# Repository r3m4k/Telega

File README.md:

# Telega

## Структура проекта

Проект состоит из нескольких самостоятельных частей:

- `Embedded` - прошивка для STM32F3Discovery, протокол обмена, драйверы датчиков и прикладная логика МК.
- `Python` - GUI-приложение для ПК, слой связи с МК, сохранение данных и вспомогательные модули анализа.
- `KiCad` - файлы печатной платы. В рамках этого README описывается только наличие раздела, без разбора содержимого.
- `Kompas3d` - механические модели и сборки. Файлы CAD не анализируются подробно.
- `Список комплектующих.csv` - перечень компонентов проекта.

## GUI-приложение для ПК

GUI находится в каталоге `Python` и запускается из `Python/main.py`. Приложение написано на PyQt5 и предназначено для работы с путеизмерительной тележкой через COM-порт: настройка подключения, запуск служебных стадий МК, отображение текущих показаний и сохранение результатов измерений.

### Запуск

Рекомендуемый запуск из корня репозитория:

```bash
python -m venv Python/.venv
Python/.venv/Scripts/pip install -r Python/requirements.txt
Python/.venv/Scripts/python Python/main.py
```

На Linux путь к интерпретатору виртуального окружения будет `Python/.venv/bin/python`.

### Возможности приложения

- выбор директории сохранения и шаблона имени файлов;
- выбор и обновление списка COM-портов;
- запуск рукопожатия с МК после применения настроек;
- запуск набора статического буфера перед проездом;
- запуск и завершение измерительного проезда;
- отображение текущих значений `Acc_X`, `Acc_Y`, `Acc_Z`, `Gyro_X`, `Gyro_Y`, `Gyro_Z` и кода ДПП;
- сохранение данных статического буфера и проезда в CSV;
- вывод пользовательских сообщений, предупреждений и ошибок в журнале окна.

Типовой рабочий сценарий описан подробнее в `Python/docs/USER_GUIDE.md`.

### Основные модули

- `Python/main.py` - точка входа, создание `QApplication` и главного окна.
- `Python/gui/main_window.py` - главное окно, координирующее интерфейс, сессию связи и переключение пользовательских стадий.
- `Python/gui/program_stages` - реализации стадий настройки, статического буфера и измерений, а также контракт главного окна, необходимый этим стадиям.
- `Python/gui/ui/main_window.ui` - Qt Designer-разметка интерфейса; рядом лежат графические ресурсы `telega.png` и `update.png`.
- `Python/gui/com_port_settings.py` и `Python/gui/saving_params.py` - работа с настройками COM-порта и параметрами сохранения.
- `Python/gui/com_port_reader.py` - мост между GUI и низкоуровневой сессией МК. Запускает отдельный процесс для обмена с устройством и прокидывает данные/события в GUI через Qt-сигналы.
- `Python/telega_session/data_storage.py` - потоковая запись пакетов `TelegaData` в CSV в дочерней сессии МК.
- `Python/gui/data_visualization.py` - обновление LCD-индикаторов текущими значениями телеметрии.
- `Python/telega_session` - проектный слой общения с тележкой: COM-порт, декодер протокола, контроллер команд и функция запуска сессии.
- `Python/async_mc_controller` - более общий асинхронный слой для источников байтов, декодирования, контроллера, шины сигналов, логирования и конфигурации.
- `Python/app_config` и `Python/logger` - конфигурация приложения на Pydantic и настройка логирования.
- `Python/data_analys` и `Python/plotting` - вспомогательные модули для постобработки, фильтрации, расчета траектории и построения графиков.

### Поток данных

После применения настроек главное окно создаёт конфигурацию COM-порта и запускает `ComPortReader`. Низкоуровневая сессия работает в отдельном процессе через `multiprocessing`, читает байтовый поток с устройства, декодирует пакеты протокола и потоково сохраняет их в CSV. В GUI передаётся только последний пакет не чаще одного раза в 500 мс для обновления индикаторов; служебные события и ошибки передаются отдельной очередью. Главное окно задаёт путь CSV-файла и переключает доступные действия пользователя согласно текущей стадии работы.

### Сохраняемые данные

Во время набора статического буфера создается файл вида:

```text
{шаблонное_название}_static_init_{номер_проезда}.csv
```

Во время измерительного проезда создается файл вида:

```text
{шаблонное_название}_measuring_{номер_проезда}.csv
```

CSV пишется в UTF-8 с полями:

```text
PackageNum DppCode AccX AccY AccZ GyroX GyroY GyroZ Temp
```

Настройки приложения сохраняются в `Python/app_config/settings.json`; файл относится к локальным runtime-данным и не обязан храниться в репозитории.

## Прошивка для STM32F3Discovery

Пользовательская часть прошивки расположена в `Embedded/user` и написана как C++-слой поверх STM32F30x Standard Peripheral Library, USB VCP и библиотек датчиков платы STM32F3Discovery. Проект устроен почти как header-only фреймворк: прикладной сценарий находится в `src/main.cpp`, а драйверы, контейнеры, фильтры, протоколы и обвязка периферии вынесены в заголовочные модули `inc`.

### Общая структура

- `src/main.cpp` - точка входа, инициализация оборудования, главный цикл, стадии программы, обработчики команд и системные функции.
- `inc/main.h` - C/C++ мост к STM32 SPL, USB VCP, CMSIS и функциям пользовательского слоя.
- `inc/Common` - общие типы, константы, `TriaxialData` и базовый механизм регистрации обработчиков прерываний.
- `inc/Periph` - GPIO, EXTI и светодиоды платы.
- `inc/Timers` - обертки над аппаратными таймерами STM32, конфигурации и descriptor-классы.
- `inc/Sensors` - драйверы L3GD20, LSM303DLHC и масштабирование датчиков.
- `inc/Filters` - статистика, N-sigma фильтр и фильтр Калмана.
- `inc/DataContainers` - очереди фиксированного размера, включая SPSC-очередь для обмена между IRQ и main.
- `inc/Communication` - сообщения, пакеты, декодеры, USB VCP и USART.
- `inc/aaa_Project_Files` - доменная логика проекта: команды, пакет телеметрии, декодер входящих команд и датчик пройденного пути.

### Инициализация и прерывания

При старте `main()` копирует таблицу векторов прерываний из flash в пользовательскую таблицу `_user_vector_table` в RAM, переключает `SCB->VTOR` на эту таблицу и затем инициализирует оборудование через `InitAll()`. Такой подход позволяет C++-объектам регистрировать собственные обработчики IRQ во время инициализации.

Механизм регистрации прерываний реализован через CRTP-класс `BaseIRQDevice`. Конкретные устройства, например таймеры или EXTI-пины, наследуются от него, сохраняют указатель на активный экземпляр и записывают статический обработчик в пользовательскую таблицу векторов. При срабатывании IRQ статический обработчик перенаправляет вызов в метод `irq_handler()` нужного объекта.

### Основной цикл и стадии программы

Главный цикл прошивки работает как простой диспетчер событий. Сначала он выполняет накопленные отложенные команды из `command_manager.command_queue`, затем при необходимости переключает текущую стадию из `program_stage_queue`, после чего вызывает `init()` новой стадии один раз и `execute()` на каждом проходе цикла.

Поддерживаемые стадии:

- `FooStage` - состояние ожидания: таймеры остановлены, датчики периодически читаются для поддержания их рабочего состояния.
- `StaticStage` - статический сбор начальных данных: формируется `InitFrameNum` телеметрических пакетов, после чего отправляется `END_OF_STATIC_INIT`.
- `MeasuringStage` - рабочее измерение: по тику `TIM3` читаются датчики, данные фильтруются, упаковываются и отправляются на ПК.

### Таймеры

В прошивке используются два таймера общего назначения:

- `TIM3` - основной таймер измерений. Его IRQ переключает светодиод `LED9`, выставляет флаг нового периода измерений и увеличивает счетчик времени `tick_counter`.
- `TIM4` - таймер индикации состояния. Его IRQ переключает `LED6` и `LED7`.

Таймеры описаны шаблонными классами `Timer2`, `Timer3`, `Timer4`, которые принимают пользовательский обработчик прерывания как compile-time параметр. Это позволяет вызывать обработчик без виртуальных функций и без runtime-диспетчеризации.

### Датчики и фильтрация

Прошивка работает с датчиками платы STM32F3Discovery:

- `L3GD20` - гироскоп, данные угловой скорости.
- `LSM303DLHC` - акселерометр и температурный датчик; магнитометр в текущей конфигурации отключен.
- `DppSensor` - датчик пройденного пути: импульсы приходят на EXTI-вход `PC1`, направление считывается с `PC3`.

Перед отправкой телеметрии данные акселерометра, гироскопа и температуры проходят через `NSigmaFilter`. Для ускорения и угловой скорости используется фильтр `NSigmaFilter<TriaxialData, 4, 16>`, для температуры - `NSigmaFilter<float, 1, 16>`. Фильтр отбрасывает выбросы по правилу N-sigma и накапливает итоговое среднее.

### Связь с ПК и протокол

Основной канал связи с ПК - USB Virtual COM Port. Входящие данные принимаются в `UserEP3_OUT_Callback()`, преобразуются в `Messages::SizedMessage<VCP_BUFFER_SIZE>` и передаются в `UsbPort`, где поток байтов разбирается `DecoderTelega`.

Входящий командный протокол:

- header: `0xE7 0x7E`;
- format: `0xAB`;
- length: длина поля данных;
- data: код команды;
- checksum: младший байт суммы предыдущих байтов пакета.

`DecoderTelega` отвечает только за входящий поток команд. Он находит команду в списках `urgent_commands` и `deferred_commands` менеджера команд. Срочные команды выполняются сразу в контексте обработчика приема, отложенные команды помещаются в SPSC-очередь и выполняются позже в основном цикле.

Поддерживаемые команды:

- `0xff 0xff` - перезагрузка МК.
- `0xaa 0x00` - переход в `FooStage`.
- `0xaa 0x02` - переход в `MeasuringStage`.
- `0xaa 0x03` - переход в `StaticStage`.
- `HANDSHAKE_ACK`, `HEARTBEAT_ACK` - текстовые служебные команды, на которые МК отвечает собственными ACK-сообщениями.

### Исходящие пакеты

Телеметрия отправляется через `TelegaPackage`. Пакет содержит:

- счетчик времени `tick_counter`;
- ускорение `acc_value`;
- угловую скорость `gyro_value`;
- температуру `temp_value`;
- код датчика пройденного пути `dpp_code`;
- контрольную сумму.

Текстовые служебные ответы формируются через `MessagePackage`: подтверждение команды, handshake ACK, heartbeat ACK, сообщение об ошибке и окончание статической инициализации.

### Соглашения проекта

Прошивка рассчитана на доверенный ПК-клиент, который отправляет небольшие корректные команды и не перегружает очередь команд. Переполнение очередей и чрезмерная длина входящих пакетов считаются нарушением протокольного соглашения, а не штатным режимом работы. Частота таймера измерений должна быть согласована со временем чтения датчиков, фильтрации и отправки пакета так, чтобы обработка успевала завершиться до следующего периода измерений.

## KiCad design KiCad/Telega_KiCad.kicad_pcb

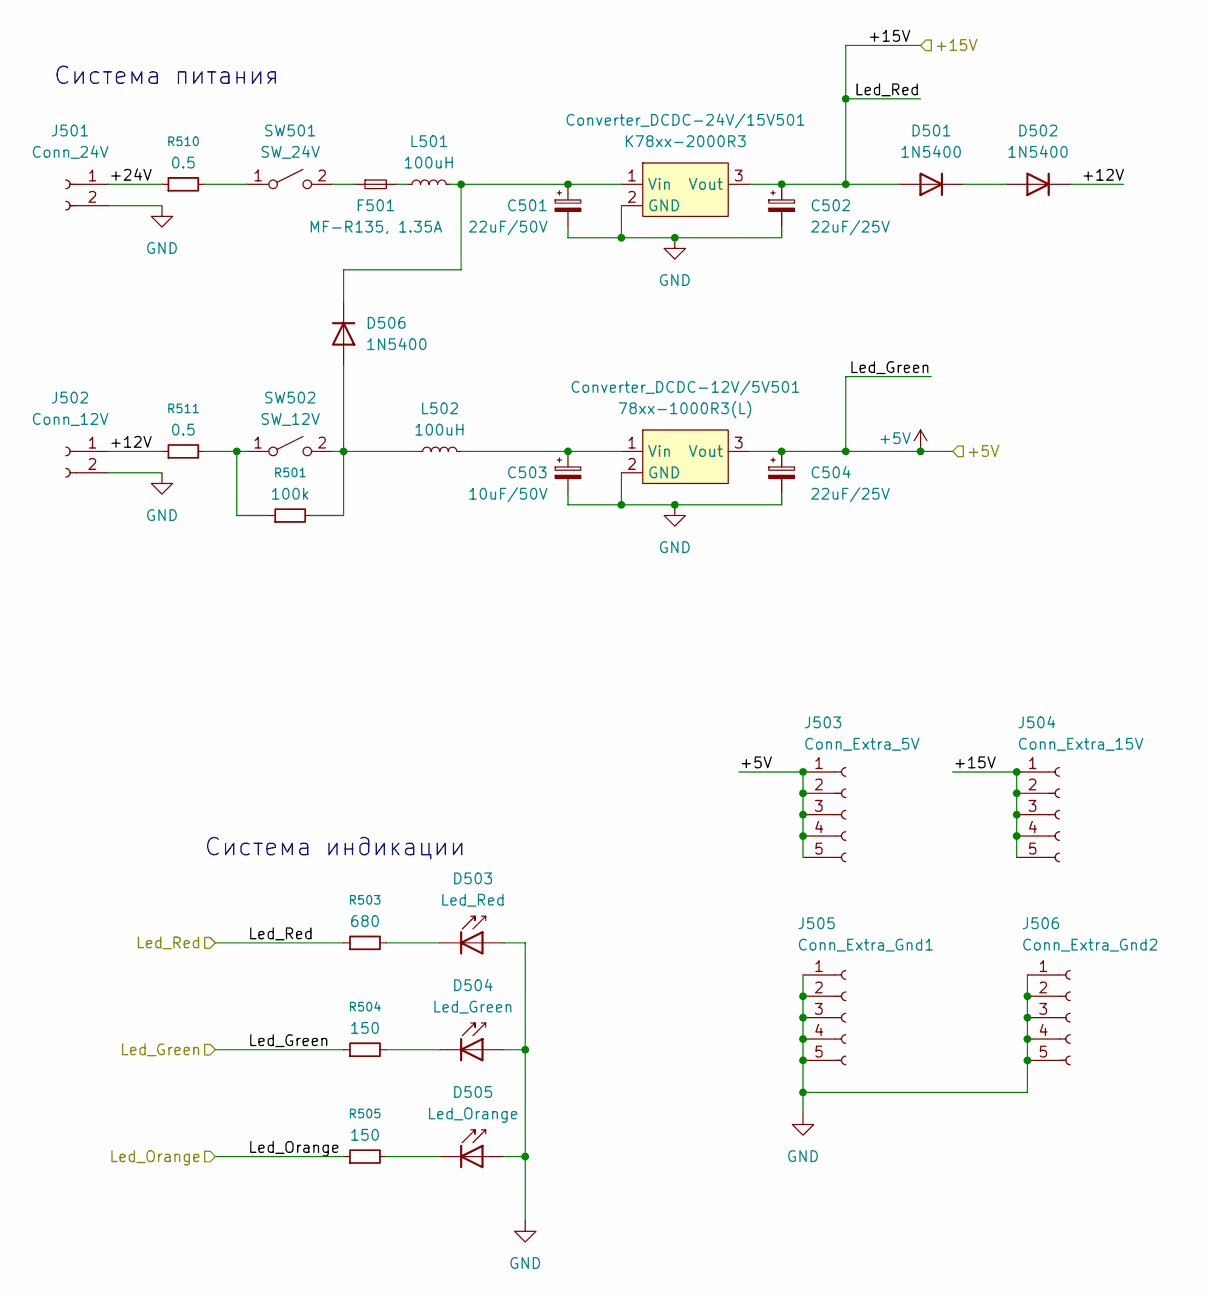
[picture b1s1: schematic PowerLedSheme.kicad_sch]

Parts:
C501: 22uF/50V; CP_Radial_D8.0mm_P5.00mm
C502, C504: 22uF/25V; CP_Radial_D8.0mm_P5.00mm
C503: 10uF/50V; CP_Radial_D8.0mm_P5.00mm
Converter_DCDC-12V/5V501: 78xx-1000R3(L); Converter_DCDC_RECOM_R-78B-2.0_THT
Converter_DCDC-24V/15V501: K78xx-2000R3; Converter_DCDC_RECOM_R-78B-2.0_THT
D501, D502, D506: 1N5400; D_DO-201AD_P15.24mm_Horizontal
D503: Led_Red; SolderWire-1sqmm_1x02_P5.4mm_D1.4mm_OD2.7mm
D504: Led_Green; SolderWire-1sqmm_1x02_P5.4mm_D1.4mm_OD2.7mm
D505: Led_Orange; SolderWire-1sqmm_1x02_P5.4mm_D1.4mm_OD2.7mm
F501: MF-R135, 1.35А; Fuse_Bourns_MF-RG300
J501: Conn_24V; Molex_KK-254_AE-6410-02A_1x02_P2.54mm_Vertical
J502: Conn_12V; Molex_KK-254_AE-6410-02A_1x02_P2.54mm_Vertical
J503: Conn_Extra_5V; SolderWire-1sqmm_1x05_P5.4mm_D1.4mm_OD2.7mm
J504: Conn_Extra_15V; SolderWire-1sqmm_1x05_P5.4mm_D1.4mm_OD2.7mm
J505: Conn_Extra_Gnd1; SolderWire-1sqmm_1x05_P5.4mm_D1.4mm_OD2.7mm
J506: Conn_Extra_Gnd2; SolderWire-1sqmm_1x05_P5.4mm_D1.4mm_OD2.7mm
L501, L502: 100uH; L_Radial_D9.5mm_P5.00mm_Fastron_07HVP
R501: 100k; R_Axial_DIN0516_L15.5mm_D5.0mm_P25.40mm_Horizontal
R503: 680; R_Axial_DIN0516_L15.5mm_D5.0mm_P25.40mm_Horizontal
R504, R505: 150; R_Axial_DIN0516_L15.5mm_D5.0mm_P25.40mm_Horizontal
R510, R511: 0.5; R_Axial_Power_L38.0mm_W6.4mm_P40.64mm
SW501: SW_24V; SolderWire-1.5sqmm_1x02_P7.8mm_D1.7mm_OD3.9mm
SW502: SW_12V; SolderWire-1.5sqmm_1x02_P7.8mm_D1.7mm_OD3.9mm

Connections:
+5V: C504.1, Converter_DCDC-12V/5V501.3 (Vout), J503.1, J503.2, J503.3, J503.4, J503.5, R504.1; also elsewhere on the board
/+15V: C502.1, Converter_DCDC-24V/15V501.3 (Vout), D501.2 (A), J504.1, J504.2, J504.3, J504.4, J504.5, R503.1; also elsewhere on the board
/Led_Orange: R505.1; also elsewhere on the board
/PowerLedSheme/+12V: D502.1 (K), J502.1, R511.1
/PowerLedSheme/+24V: J501.1, R510.1
GND: C501.2, C502.2, C503.2, C504.2, Converter_DCDC-12V/5V501.2 (GND), Converter_DCDC-24V/15V501.2 (GND), D503.2 (A), D504.2 (A), D505.2 (A), J501.2, J502.2, J505.1, J505.2, J505.3, J505.4, J505.5, J506.1, J506.2, J506.3, J506.4, J506.5; also elsewhere on the board
unnamed: C503.1, Converter_DCDC-12V/5V501.1 (Vin), L502.2
unnamed: C501.1, Converter_DCDC-24V/15V501.1 (Vin), D506.1 (K), L501.2
unnamed: D501.1 (K), D502.2 (A)
unnamed: D503.1 (K), R503.2
unnamed: D504.1 (K), R504.2
unnamed: D505.1 (K), R505.2
unnamed: D506.2 (A), L502.1, R501.2, SW502.2 (B)
unnamed: F501.2, L501.1
unnamed: R510.2, SW501.1 (A)
unnamed: F501.1, SW501.2 (B)
unnamed: R501.1, R511.2, SW502.1 (A)

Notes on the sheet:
Система питания
Система индикации

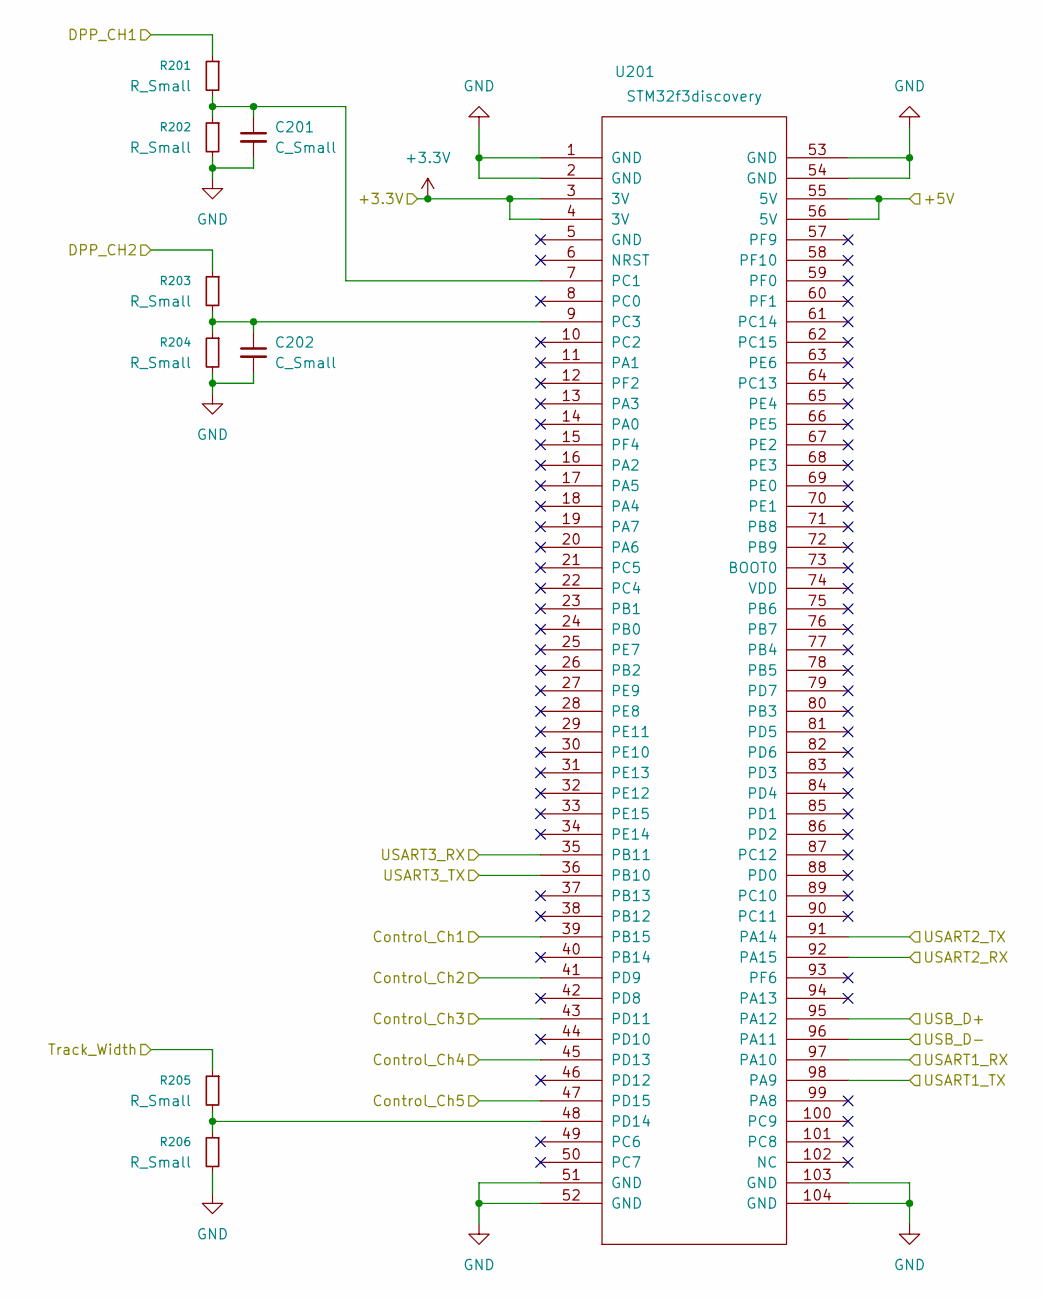
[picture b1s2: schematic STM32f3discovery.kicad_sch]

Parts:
C201, C202: C_Small; CP_Radial_D8.0mm_P5.00mm
R201, R202, R203, R204, R205, R206: R_Small; R_Axial_DIN0207_L6.3mm_D2.5mm_P15.24mm_Horizontal
U201: STM32f3discovery

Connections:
+3.3V: U201.3 (3V), U201.4 (3V)
+5V: U201.55 (5V), U201.56 (5V); also elsewhere on the board
/Control_Ch1: U201.39 (PB15); also elsewhere on the board
/Control_Ch2: U201.41 (PD9); also elsewhere on the board
/Control_Ch3: U201.43 (PD11); also elsewhere on the board
/Control_Ch4: U201.45 (PD13); also elsewhere on the board
/Control_Ch5: U201.47 (PD15); also elsewhere on the board
/DPP_CH1: R201.1; also elsewhere on the board
/DPP_CH2: R203.1; also elsewhere on the board
/Track_Width: R205.1; also elsewhere on the board
/USART1_RX: U201.97 (PA10); also elsewhere on the board
/USART1_TX: U201.98 (PA9); also elsewhere on the board
/USART2_RX: U201.92 (PA15); also elsewhere on the board
/USART2_TX: U201.91 (PA14); also elsewhere on the board
/USART3_RX: U201.35 (PB11); also elsewhere on the board
/USART3_TX: U201.36 (PB10); also elsewhere on the board
/USB_D+: U201.95 (PA12); also elsewhere on the board
/USB_D-: U201.96 (PA11); also elsewhere on the board
GND: C201.2, C202.2, R202.2, R204.2, R206.2, U201.1 (GND), U201.2 (GND), U201.51 (GND), U201.52 (GND), U201.53 (GND), U201.54 (GND), U201.103 (GND), U201.104 (GND); also elsewhere on the board
unnamed: C201.1, R201.2, R202.1, U201.7 (PC1)
unnamed: C202.1, R203.2, R204.1, U201.9 (PC3)
unnamed: R205.2, R206.1, U201.48 (PD14)

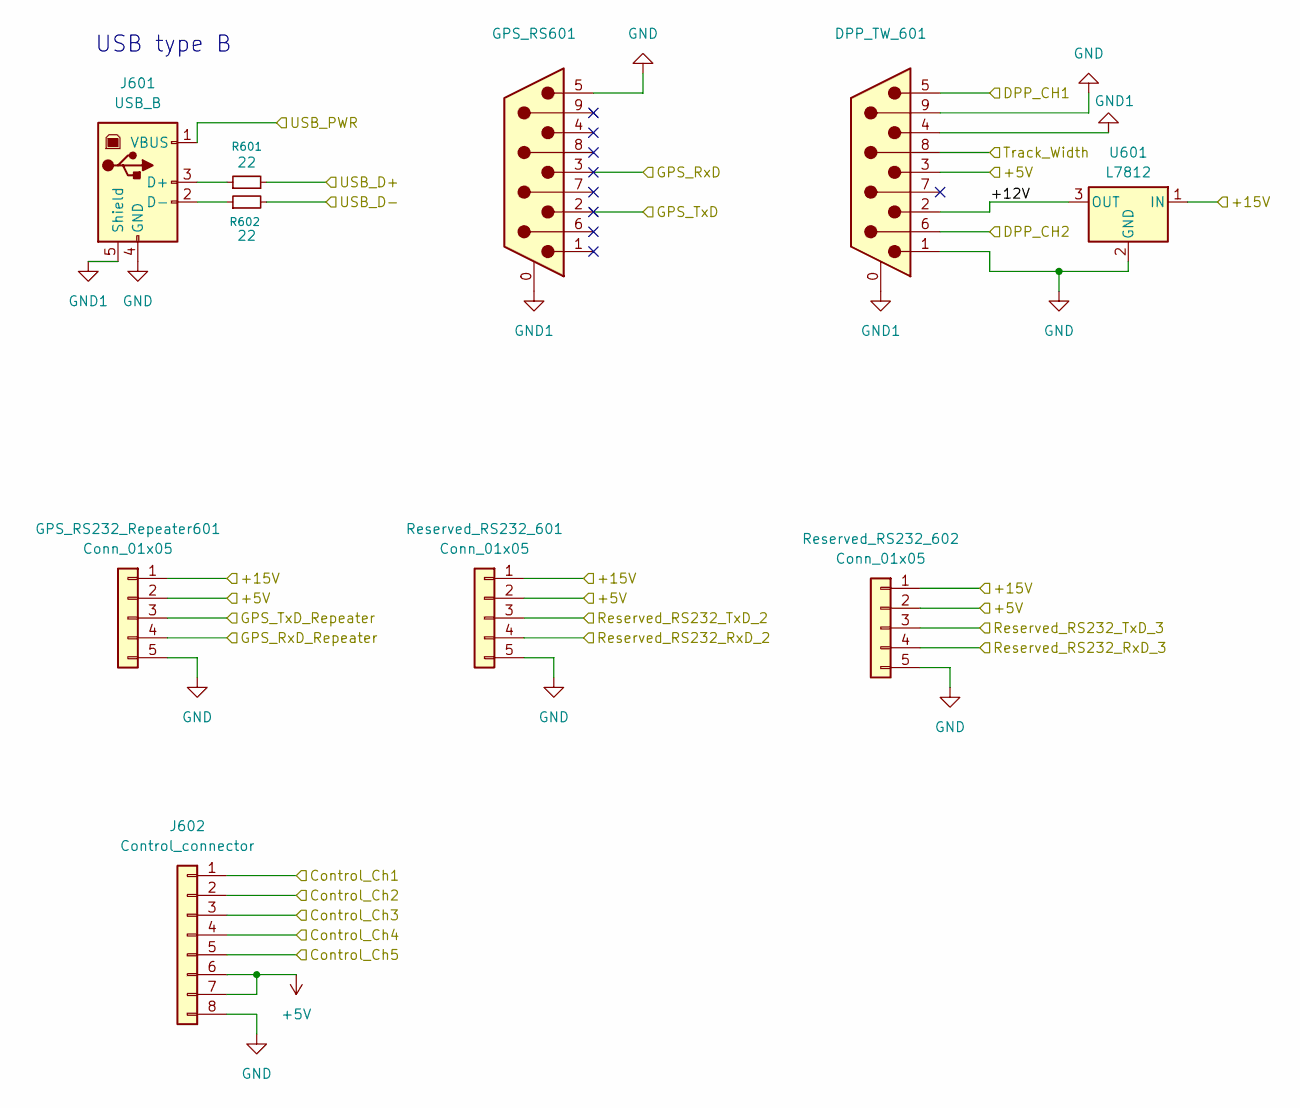
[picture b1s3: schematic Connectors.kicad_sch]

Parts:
DPP_TW_601: DE9_Pins_MountingHoles; DSUB-9_Pins_Horizontal_P2.77x2.84mm_EdgePinOffset7.70mm_Hou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
GPS_RS232_Repeater601: Conn_01x05; SolderWire-1sqmm_1x05_P5.4mm_D1.4mm_OD2.7mm
GPS_RS601: DE9_Pins_MountingHoles; DSUB-9_Pins_Horizontal_P2.77x2.84mm_EdgePinOffset7.70mm_Hou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
J601: USB_B; USB_B_Lumberg_2411_02_Horizontal
J602: Control_connector; Molex_KK-254_AE-6410-08A_1x08_P2.54mm_Vertical
R601, R602: 22; R_1206_3216Metric
Reserved_RS232_601, Reserved_RS232_602: Conn_01x05; SolderWire-1sqmm_1x05_P5.4mm_D1.4mm_OD2.7mm
U601: L7812; TO-220-3_Vertical

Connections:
+5V: DPP_TW_601.3, GPS_RS232_Repeater601.2, J602.6, J602.7, Reserved_RS232_601.2, Reserved_RS232_602.2; also elsewhere on the board
/+15V: GPS_RS232_Repeater601.1, Reserved_RS232_601.1, Reserved_RS232_602.1, U601.1 (IN); also elsewhere on the board
/Connectors/+12V: DPP_TW_601.2, U601.3 (OUT)
/Control_Ch1: J602.1; also elsewhere on the board
/Control_Ch2: J602.2; also elsewhere on the board
/Control_Ch3: J602.3; also elsewhere on the board
/Control_Ch4: J602.4; also elsewhere on the board
/Control_Ch5: J602.5; also elsewhere on the board
/DPP_CH1: DPP_TW_601.5; also elsewhere on the board
/DPP_CH2: DPP_TW_601.6; also elsewhere on the board
/GPS_RxD: GPS_RS601.3; also elsewhere on the board
/GPS_RxD_Repeater: GPS_RS232_Repeater601.4; also elsewhere on the board
/GPS_TxD: GPS_RS601.2; also elsewhere on the board
/GPS_TxD_Repeater: GPS_RS232_Repeater601.3; also elsewhere on the board
/Led_Orange: J601.1 (VBUS); also elsewhere on the board
/Reserved_RS232_RxD_2: Reserved_RS232_601.4; also elsewhere on the board
/Reserved_RS232_RxD_3: Reserved_RS232_602.4; also elsewhere on the board
/Reserved_RS232_TxD_2: Reserved_RS232_601.3; also elsewhere on the board
/Reserved_RS232_TxD_3: Reserved_RS232_602.3; also elsewhere on the board
/Track_Width: DPP_TW_601.8; also elsewhere on the board
/USB_D+: R601.2; also elsewhere on the board
/USB_D-: R602.2; also elsewhere on the board
GND: DPP_TW_601.1, DPP_TW_601.9, GPS_RS232_Repeater601.5, GPS_RS601.5, J601.4 (GND), J602.8, Reserved_RS232_601.5, Reserved_RS232_602.5, U601.2 (GND); also elsewhere on the board
GND1: DPP_TW_601.0 (PAD), DPP_TW_601.4, GPS_RS601.0 (PAD), J601.5 (Shield)
unnamed: J601.3 (D+), R601.1
unnamed: J601.2 (D-), R602.1

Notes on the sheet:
USB type B

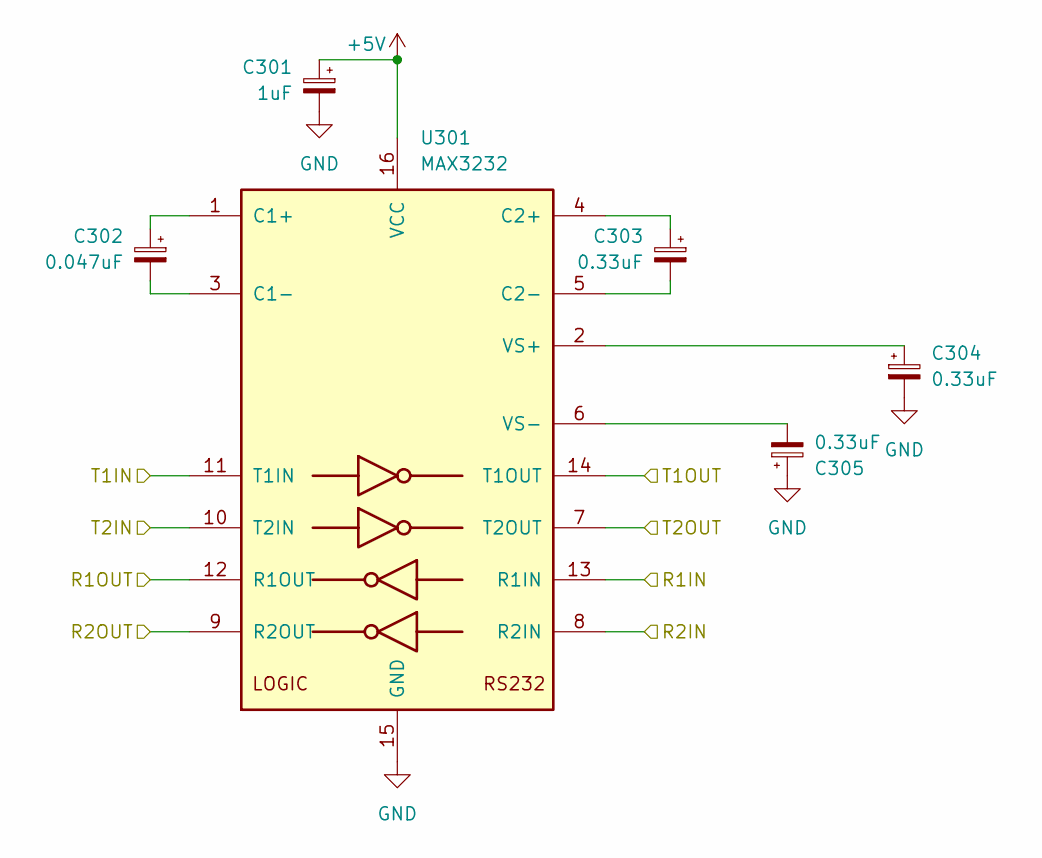
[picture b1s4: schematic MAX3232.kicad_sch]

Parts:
C301: 1uF; CP_EIA-2012-12_Kemet-R_HandSolder
C302: 0.047uF; CP_EIA-2012-12_Kemet-R_HandSolder
C303, C304, C305: 0.33uF; CP_EIA-2012-12_Kemet-R_HandSolder
U301: MAX3232; SOIC-16W_7.5x10.3mm_P1.27mm

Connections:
+5V: C301.1, U301.16 (VCC); also elsewhere on the board
/GPS_RxD: U301.14 (T1OUT); also elsewhere on the board
/GPS_RxD_Repeater: U301.7 (T2OUT); also elsewhere on the board
/GPS_TxD: U301.13 (R1IN); also elsewhere on the board
/GPS_TxD_Repeater: U301.8 (R2IN); also elsewhere on the board
/USART1_RX: U301.9 (R2OUT), U301.12 (R1OUT); also elsewhere on the board
/USART1_TX: U301.10 (T2IN), U301.11 (T1IN); also elsewhere on the board
GND: C301.2, C304.2, C305.1, U301.15 (GND); also elsewhere on the board
unnamed: C302.1, U301.1 (C1+)
unnamed: C302.2, U301.3 (C1-)
unnamed: C303.1, U301.4 (C2+)
unnamed: C303.2, U301.5 (C2-)
unnamed: C304.1, U301.2 (VS+)
unnamed: C305.2, U301.6 (VS-)

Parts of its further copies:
C401: 1uF; CP_EIA-2012-12_Kemet-R_HandSolder
C402: 0.047uF; CP_EIA-2012-12_Kemet-R_HandSolder
C403, C404, C405: 0.33uF; CP_EIA-2012-12_Kemet-R_HandSolder
U401: MAX3232; SOIC-16W_7.5x10.3mm_P1.27mm

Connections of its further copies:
+5V: C401.1, U401.16 (VCC); also elsewhere on the board
/Reserved_RS232_RxD_2: U401.14 (T1OUT); also elsewhere on the board
/Reserved_RS232_RxD_3: U401.7 (T2OUT); also elsewhere on the board
/Reserved_RS232_TxD_2: U401.13 (R1IN); also elsewhere on the board
/Reserved_RS232_TxD_3: U401.8 (R2IN); also elsewhere on the board
/USART2_RX: U401.12 (R1OUT); also elsewhere on the board
/USART2_TX: U401.11 (T1IN); also elsewhere on the board
/USART3_RX: U401.9 (R2OUT); also elsewhere on the board
/USART3_TX: U401.10 (T2IN); also elsewhere on the board
GND: C401.2, C404.2, C405.1, U401.15 (GND); also elsewhere on the board
unnamed: C402.1, U401.1 (C1+)
unnamed: C402.2, U401.3 (C1-)
unnamed: C403.1, U401.4 (C2+)
unnamed: C403.2, U401.5 (C2-)
unnamed: C404.1, U401.2 (VS+)
unnamed: C405.2, U401.6 (VS-)

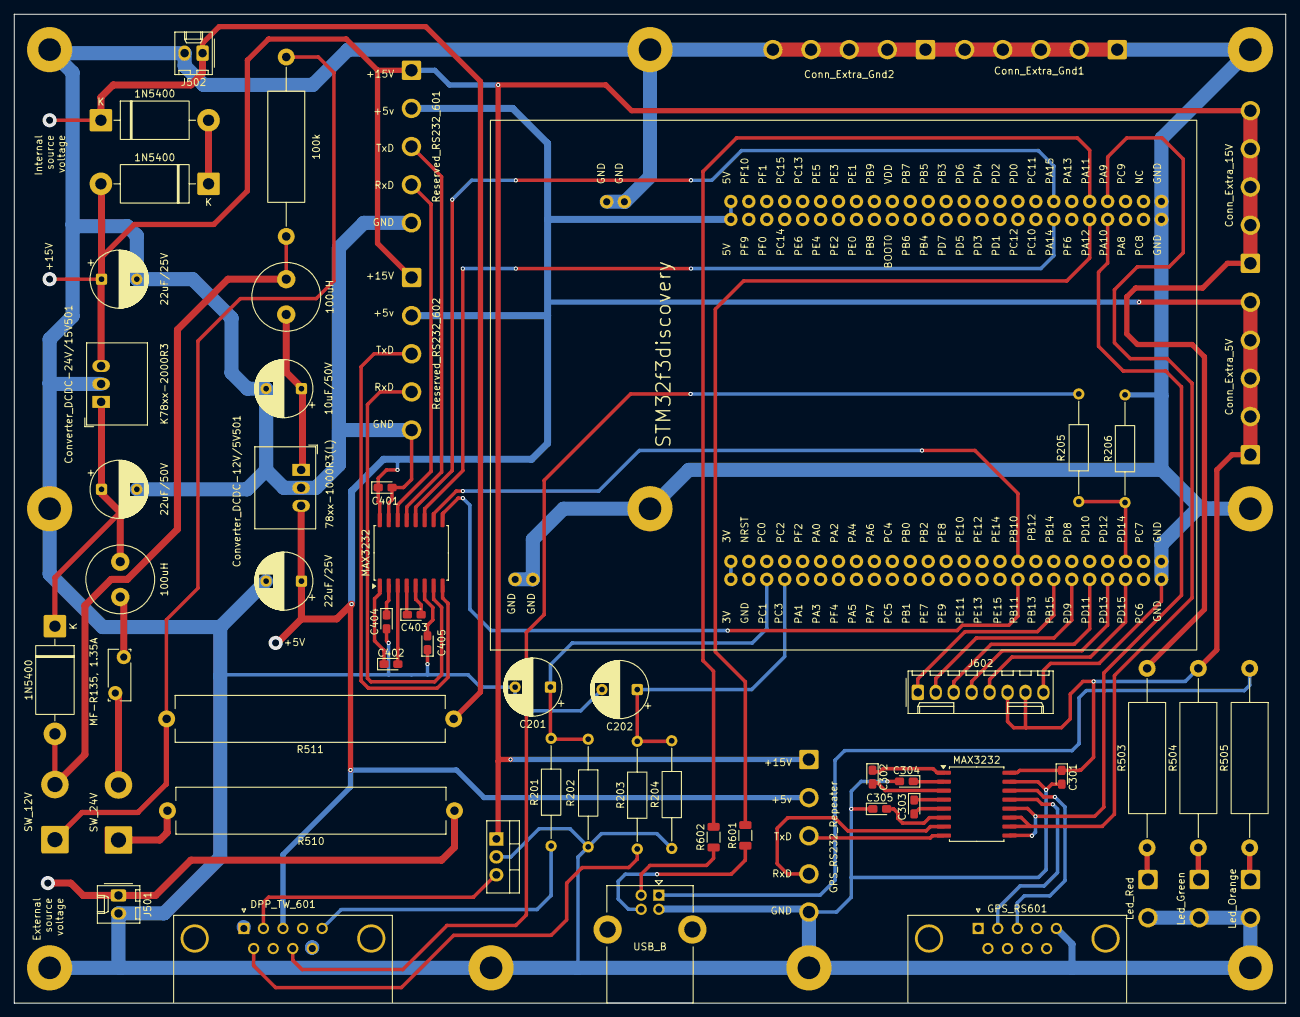
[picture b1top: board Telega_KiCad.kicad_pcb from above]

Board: 2 copper layers, 180.0 x 140.0 mm, 60 parts (0 on the bottom side), 61 nets.

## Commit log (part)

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2025-04-07 Создал основную часть GUI для сбора данных
2025-04-10 Начало реализации мультипроцессорной логики программы
2025-04-10 Реализовал многопроцессорную логику
2025-04-11 Реализовал декодирование данных из COM порта в отдельном процессе
    Надо исправить, хех
2025-04-12 Реализовано корректное чтение данных из COM порта и последующее сохранение
2025-04-14 Сделал отображение полученных данных на графиках
2025-04-14 Изменён вывод программы
2025-04-18 Добавлено подключение GPS модуля с помощью QCheckBox
2025-04-21 Добавлены обработчик ошибок из других процессов и логирование работы программы
    Обработчик реализован обработкой текстовых сообщений из общей очереди сообщений
2025-04-21 Улучшена обработка исключений, которые могут возникнуть в ходе работы программы
2025-04-30 Начал реализовывать класс COM_Port, как дочерний класс Process
2025-04-30 Откат :(
    Нужно создать систему сигналов между процессами
2025-05-05 Вроде как сделал систему сигналов между процессами
    Сделал на основе очереди
2025-05-05 Реализована система сигналов между процессами с помощью Pipes
    Не уверен, что это лучше чем Queue, но пусть будет для разнообразия
2025-05-05 Обновил gitignore
2025-05-05 Реализовано подтверждение полученных сообщений
2025-05-06 Реализована выставка датчиков
2025-05-19 Начал разделение классов для работы с STM и GPS
2025-05-19 Завершено разделение классов для работы с STM и GPS
2025-06-04 Убрал построение графиков в реальном времени
2025-06-06 Убрал лишний закоменченный код
2025-06-09 Добавил кнопку перезапуска платы
2025-06-24 Добавил индикацию работы программы
2025-06-24 Изменение индикатора
2025-06-30 Изменение поведения при перезепуске платы
2025-06-30 Добавил проверку существования директории из json файла
2025-06-30 Начал реализацию обработки данных
2025-07-01 Создал класс для гибкого создания графиков и работы с ними
2025-07-02 Добавил задание COM порта для STM по hwid прошлого устройства
2025-07-02 Добавил фильтр Калмана и построение графиков всех исходных данных
2025-07-03 Добавил построение графиков с гистограммами нулевых данных
2025-07-03 Реализовал настройку шагов обработки данных с помощью передаваемого словаря
2025-07-04 Добавил автоматическую классификацию файлов и дополнительный информационный вывод
2025-07-25 Вынес логику построения графиков в отдельный класс
2025-08-08 Добавил свой сглаживающий фильтр и начал реализацию учёта поворота телеги
2025-08-13 Начал реализацию алгоритма учёта вращения платы
2025-08-13 Реализовал алгоритм учёта вращения платы
    Нужно сделать вычисление скорости и понять адекватность полученных результатов
2025-08-14 Добавил функцию сохранения в csv файл
2025-08-21 Изменил gitignore
2025-08-22 Проведена реструктуризация проекта
2025-08-22 Изменил относительные импорты в модулях
2025-08-25 Начал переделывать логику взаимодействия с COM портом
2025-08-26 Закончил рефакторинг кода для работы с платой STM32f3discovery через COM-порт
2025-10-16 Собрал все файлы из разных директорий в одно место
2025-10-16 Выровнял посадочные места на плате
2025-10-16 Сохранение файлов программы
2025-10-16 Создал первую эскизную сборку
2025-10-21 Начал проектировать второй вариант корпуса
2025-10-30 Обрезал основание платы под крепление в коробке
2026-01-27 Редактирование платы
    Я не помню, что тут изменил...
2026-01-27 Спроектировал переднюю панель
2026-01-29 Реализовал статическую очередь
2026-02-10 Перенёс все файлы из другого проекта
2026-02-12 Реализовать NSigmaFilter
2026-02-12 Рефакторинг файлов для работы с таймерами
2026-02-13 Переделал выполнение switch (stage)
2026-02-13 Небольшой рефакторинг main.cpp
2026-02-16 Добавил декодер получаемых сообщений
2026-02-17 Реализовал поддержку float в классе NSigmaFilter для фильтрации температуры из main
2026-02-17 Изменил название директории
2026-02-17 Получилось собрать проект
2026-02-18 Модифицировал классы Message и TriaxialData
2026-02-19 Убрал лишние файлы
2026-02-19 Рефакторинг
2026-02-24 Обновил TriaxialData
2026-02-27 Добавил пакет decoding для более удобного декодирования входного потока данных
2026-02-27 Проверил работоспособность с дополнительным декодером
2026-02-27 Изменил вычисление длины полезных данных в пакете данных
2026-03-16 Начал создание алгоритма расчёта траектории движения
2026-03-16 Доработал модель передней панели
2026-03-16 Создал модели крепления АКБ и корпуса к телеге
2026-03-31 Реализовал описанный в дипломе алгоритм построения траектории движения
2026-04-03 Перенёс дополнительные файлы
2026-05-06 Перенёс файлы из AsyncMCController/Embedded
2026-05-06 Исправил инициализацию VCP
2026-05-06 Исправил ACK сообщения
2026-05-06 Уменьшил габариты панели и добавил фаски
2026-05-06 Добавил CalibrationStage для установления масштабирующего коэффициента датчиков
    Вызывается по бинарной команде 0xaa, 0x01
2026-05-06 Исправил ошибки для корректной сборки
2026-05-11 Добавил send_end_of_calibration_msg и изменил список срочных команд
2026-05-12 Обновил крепления к тележке
2026-05-13 Исправил получаемые команды
2026-05-14 Доработана логика выполнения стадий программ
2026-05-14 Обновил размеры на лицевой панели
2026-05-19 Добавил использование датчика ДПП
2026-05-19 Сгенерировал readme с описанием архитектуры прошивки
2026-05-19 Перенёс файлы из Telega_GUI_v2
2026-05-19 Обновлён README.md с описанием структуры GUI и обновлён .gitignore
    Перед началом работы в других ветках необходимо выполнить merge master
2026-05-20 Сгенерировал код для реализации навигационного алгоритма
2026-05-21 Вынес опрос ДПП через таймер
2026-05-21 Изменил параметры гироскопа
2026-05-22 Добавил сохранение температуры в csv файл и убрал вывод логгера в консоль
2026-05-23 Сгенерировал файл для запуска пайплайна
2026-05-28 Добавлены файлы для обработки файлов
2026-05-28 Исправил выравнивание таблицы векторов прерывания и инициализацию EXTI
